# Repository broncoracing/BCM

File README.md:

# Body Control Module
## BR23+ BCM

### Functions:
- Control cooling
  - Fan
  - Water pump
- Actuate shifting
  - Receive shift data over CAN
  - Activate pneumatic shifting actuators
- Any other CAN-controlled outputs

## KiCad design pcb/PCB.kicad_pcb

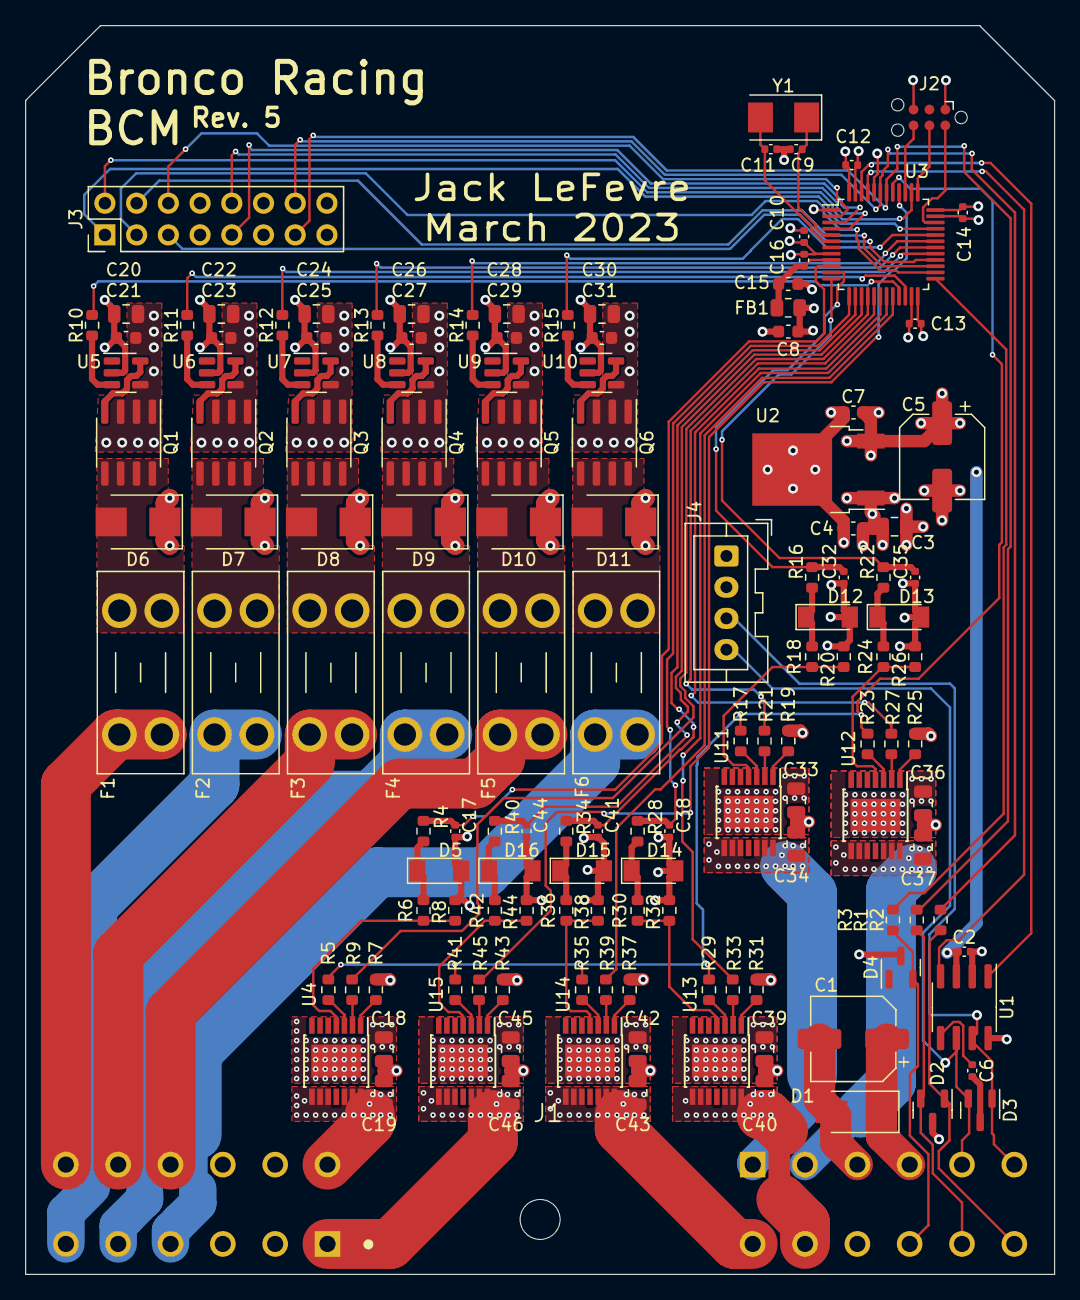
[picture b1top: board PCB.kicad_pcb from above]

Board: 4 copper layers, 82.4 x 100.0 mm, 141 parts (0 on the bottom side), 108 nets.

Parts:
C1, C5: 100uF; CP_Elec_6.3x7.7
C2, C6, C10, C12, C13, C14, C16: 100n; C_0402_1005Metric
C3, C20, C22, C24, C26, C28, C30: 2.2uF; C_0805_2012Metric
C4, C7, C21, C23, C25, C27, C29, C31: 100nF; C_0603_1608Metric
C8: 4u7; C_0603_1608Metric
C9, C11: 30p; C_0402_1005Metric
C15: 1u; C_0603_1608Metric
C17, C32, C35, C38, C41, C44: 220p; C_0402_1005Metric
C18, C33, C36, C39, C42, C45: 100nF >25V; C_0805_2012Metric
C19, C34, C37, C40, C43, C46: 10nF >25V; C_0805_2012Metric
D1: 15-25V; D_SMA
D2, D4: SP0502BAHT; SOT-23
D3: ESDCAN02-2BWY; SOT-23
D5, D12, D13, D14, D15, D16: 7V; D_MiniMELF
D6, D7, D8, D9, D10, D11: SSB43L; D_SMB
F1, F2, F3, F4, F5, F6: Fuse; Fuseholder_Blade_Mini_Keystone_3568
FB1: 100R@100MHz; R_0805_2012Metric
H1: MountingHole_3.2mm_M3
J1: DTM1312PA12PBR008; TE_DTM1312PA12PBR008
J2: TC2030; Tag-Connect_TC2030-IDC-NL_2x03_P1.27mm_Vertical
J3: Conn_02x08_Top_Bottom; PinHeader_2x08_P2.54mm_Vertical
J4: JST B04B-XASK; JST_XA_B04B-XASK-1_1x04_P2.50mm_Vertical
Q1, Q2, Q3, Q4, Q5, Q6: Si4162DY; SOIC-8_3.9x4.9mm_P1.27mm
R1, R2, R3: 470; R_0603_1608Metric
R4, R5, R6, R7, R10, R11, R12, R13, R14, R15, R16, R17, R18, R19, R22, R23, R24, R25, R28, R29, R30, R31, R34, R35, R36, R37, R40, R41, R42, R43: 4.7k; R_0603_1608Metric
R8, R20, R26, R32, R38, R44: 1.2k; R_0603_1608Metric
R9, R21, R27, R33, R39, R45: 47; R_0603_1608Metric
U1: SN65HVD230; SOIC-8_3.9x4.9mm_P1.27mm
U2: LF33_TO252; TO-252-2
U3: STM32F103C8T6; LQFP-48_7x7mm_P0.5mm
U4, U11, U12, U13, U14, U15: BTS7004-1EPP; Infineon_PG-TSDSO-14-22
U5, U6, U7, U8, U9, U10: MCP1416; SOT-23-5
Y1: 8MHz; Crystal_SMD_5032-2Pin_5.0x3.2mm

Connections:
+3.3VA: C15.1, C16.1, FB1.2, U3.9 (VDDA)
+3V3: C2.1, C5.1, C7.1, C8.1, C10.1, C12.1, C13.1, C14.1, FB1.1, J2.1 (VCC), J3.8, J3.16, U1.3 (VCC), U2.3 (VO), U3.1 (VBAT), U3.24 (VDD), U3.36 (VDD), U3.48 (VDD)
+12V: C1.1, C3.1, C4.1, C18.1, C20.1, C21.1, C22.1, C23.1, C24.1, C25.1, C26.1, C27.1, C28.1, C29.1, C30.1, C31.1, C33.1, C36.1, C39.1, C42.1, C45.1, D1.1 (A1), D6.1 (K), D7.1 (K), D8.1 (K), D9.1 (K), D10.1 (K), D11.1 (K), J1.A3, J1.A10, J1.B4, J4.1, U2.1 (VI), U4.15 (VS), U5.2 (Vdd), U6.2 (Vdd), U7.2 (Vdd), U8.2 (Vdd), U9.2 (Vdd), U10.2 (Vdd), U11.15 (VS), U12.15 (VS), U13.15 (VS), U14.15 (VS), U15.15 (VS)
/High-side Channel 0/DEN: R5.1, R17.1, R23.1, R29.1, R35.1, R41.1, U3.41 (PB5)
/High-side Channel 0/Drive: R7.1, U3.16 (PA6)
/High-side Channel 0/Sense: C17.1, R4.1, U3.10 (PA0)
/High-side Channel 1/Drive: R19.1, U3.17 (PA7)
/High-side Channel 1/Sense: C32.1, R16.1, U3.11 (PA1)
/High-side Channel 2/Drive: R25.1, U3.18 (PB0)
/High-side Channel 2/Sense: C35.1, R22.1, U3.12 (PA2)
/High-side Channel 3/Drive: R31.1, U3.19 (PB1)
/High-side Channel 3/Sense: C38.1, R28.1, U3.13 (PA3)
/High-side Channel 4/Drive: R37.1, U3.20 (PB2)
/High-side Channel 4/Sense: C41.1, R34.1, U3.14 (PA4)
/High-side Channel 5/Drive: R43.1, U3.40 (PB4)
/High-side Channel 5/Sense: C44.1, R40.1, U3.15 (PA5)
/Low-side channel 0/Drive: R10.1, U3.21 (PB10)
/Low-side channel 1/Drive: R11.1, U3.22 (PB11)
/Low-side channel 2/Drive: R12.1, U3.29 (PA8)
/Low-side channel 3/Drive: R13.1, U3.30 (PA9)
/Low-side channel 4/Drive: R14.1, U3.31 (PA10)
/Low-side channel 5/Drive: R15.1, U3.32 (PA11)
/STM32/GPIO: R3.1, U3.25 (PB12)
/STM32/HSE_IN: C11.1, U3.6 (PD1), Y1.2
/STM32/HSE_OUT: C9.1, U3.5 (PD0), Y1.1
/STM32/UART_RX: J3.13, R2.1, U3.42 (PB6)
/STM32/UART_TX: J3.14, R1.2, U3.43 (PB7)
/STM32/UU0: J3.1, U3.33 (PA12)
/STM32/UU1: J3.2, U3.38 (PA15)
/STM32/UU2: J3.3, U3.26 (PB13)
/STM32/UU3: J3.4, U3.27 (PB14)
/STM32/UU4: J3.5, U3.28 (PB15)
/STM32/UU5: J3.6, U3.2 (PC13)
/STM32/UU6: J3.9, U3.3 (PC14)
/STM32/UU7: J3.10, U3.4 (PC15)
CAN+: D3.1 (K), J1.B6, J4.3, U1.7 (CANH)
CAN-: D3.2 (K), J1.B5, J4.4, U1.6 (CANL)
CANRX: U1.4 (R), U3.45 (PB8)
CANTX: U1.1 (D), U3.46 (PB9)
GND: C1.2, C2.2, C3.2, C4.2, C5.2, C7.2, C8.2, C9.2, C10.2, C11.2, C12.2, C13.2, C14.2, C15.2, C16.2, C17.2, C18.2, C19.2, C20.2, C21.2, C22.2, C23.2, C24.2, C25.2, C26.2, C27.2, C28.2, C29.2, C30.2, C31.2, C32.2, C33.2, C34.2, C35.2, C36.2, C37.2, C38.2, C39.2, C40.2, C41.2, C42.2, C43.2, C44.2, C45.2, C46.2, D1.2 (A2), D2.3 (A), D4.3 (A), D5.2 (A), D12.2 (A), D13.2 (A), D14.2 (A), D15.2 (A), D16.2 (A), J1.A2, J1.A11, J1.B3, J1.B10, J2.5 (GND), J3.7, J3.12, J3.15, J4.2, Q1.1 (S), Q1.2 (S), Q1.3 (S), Q2.1 (S), Q2.2 (S), Q2.3 (S), Q3.1 (S), Q3.2 (S), Q3.3 (S), Q4.1 (S), Q4.2 (S), Q4.3 (S), Q5.1 (S), Q5.2 (S), Q5.3 (S), Q6.1 (S), Q6.2 (S), Q6.3 (S), R8.2, R9.2, R20.2, R21.2, R26.2, R27.2, R32.2, R33.2, R38.2, R39.2, R44.2, R45.2, U1.2 (GND), U1.8 (Rs), U2.2 (GND), U3.8 (VSSA), U3.23 (VSS), U3.35 (VSS), U3.44 (BOOT0), U3.47 (VSS), U5.4 (GND), U6.4 (GND), U7.4 (GND), U8.4 (GND), U9.4 (GND), U10.4 (GND)
H0: C19.1, J1.A12, U4.8 (OUT), U4.9 (OUT), U4.10 (OUT), U4.12 (OUT), U4.13 (OUT), U4.14 (OUT)
H1: C34.1, J1.B1, U11.8 (OUT), U11.9 (OUT), U11.10 (OUT), U11.12 (OUT), U11.13 (OUT), U11.14 (OUT)
H2: C37.1, J1.B2, U12.8 (OUT), U12.9 (OUT), U12.10 (OUT), U12.12 (OUT), U12.13 (OUT), U12.14 (OUT)
H3: C40.1, J1.B11, U13.8 (OUT), U13.9 (OUT), U13.10 (OUT), U13.12 (OUT), U13.13 (OUT), U13.14 (OUT)
H4: C43.1, J1.B12, U14.8 (OUT), U14.9 (OUT), U14.10 (OUT), U14.12 (OUT), U14.13 (OUT), U14.14 (OUT)
H5: C46.1, J1.A1, U15.8 (OUT), U15.9 (OUT), U15.10 (OUT), U15.12 (OUT), U15.13 (OUT), U15.14 (OUT)
IO: D4.2 (K), J1.B9, R3.2
L0: F1.2, J1.A7
L1: F2.2, J1.A6
L2: F3.2, J1.A8
L3: F4.2, J1.A5
L4: F5.2, J1.A9
L5: F6.2, J1.A4
unnamed: C6.1, U1.5 (Vref)
unnamed: C6.2, D3.3 (A)
unnamed: D5.1 (K), R4.2, R6.2
unnamed: D6.2 (A), F1.1, Q1.5 (D), Q1.6 (D), Q1.7 (D), Q1.8 (D)
unnamed: D7.2 (A), F2.1, Q2.5 (D), Q2.6 (D), Q2.7 (D), Q2.8 (D)
unnamed: D8.2 (A), F3.1, Q3.5 (D), Q3.6 (D), Q3.7 (D), Q3.8 (D)
unnamed: D9.2 (A), F4.1, Q4.5 (D), Q4.6 (D), Q4.7 (D), Q4.8 (D)
unnamed: D10.2 (A), F5.1, Q5.5 (D), Q5.6 (D), Q5.7 (D), Q5.8 (D)
unnamed: D11.2 (A), F6.1, Q6.5 (D), Q6.6 (D), Q6.7 (D), Q6.8 (D)
unnamed: D12.1 (K), R16.2, R18.2
unnamed: D13.1 (K), R22.2, R24.2
unnamed: D14.1 (K), R28.2, R30.2
unnamed: D15.1 (K), R34.2, R36.2
unnamed: D16.1 (K), R40.2, R42.2
unnamed: Q1.4 (G), U5.5 (OUT)
unnamed: Q2.4 (G), U6.5 (OUT)
unnamed: Q3.4 (G), U7.5 (OUT)
unnamed: Q4.4 (G), U8.5 (OUT)
unnamed: Q5.4 (G), U9.5 (OUT)
unnamed: Q6.4 (G), U10.5 (OUT)
unnamed: R5.2, U4.3 (DEN)
unnamed: R6.1, R8.1, U4.4 (IS)
unnamed: R7.2, U4.2 (IN)
unnamed: R9.1, U4.1 (GND)
unnamed: R10.2, U5.3 (IN)
unnamed: R11.2, U6.3 (IN)
unnamed: R12.2, U7.3 (IN)
unnamed: R13.2, U8.3 (IN)
unnamed: R14.2, U9.3 (IN)
unnamed: R15.2, U10.3 (IN)
unnamed: R17.2, U11.3 (DEN)
unnamed: R18.1, R20.1, U11.4 (IS)
unnamed: R19.2, U11.2 (IN)
unnamed: R21.1, U11.1 (GND)
unnamed: R23.2, U12.3 (DEN)
unnamed: R24.1, R26.1, U12.4 (IS)
unnamed: R25.2, U12.2 (IN)
unnamed: R27.1, U12.1 (GND)
unnamed: R29.2, U13.3 (DEN)
unnamed: R30.1, R32.1, U13.4 (IS)
unnamed: R31.2, U13.2 (IN)
unnamed: R33.1, U13.1 (GND)
unnamed: R35.2, U14.3 (DEN)
unnamed: R36.1, R38.1, U14.4 (IS)
unnamed: R37.2, U14.2 (IN)
unnamed: R39.1, U14.1 (GND)
unnamed: R41.2, U15.3 (DEN)
unnamed: R42.1, R44.1, U15.4 (IS)
unnamed: R43.2, U15.2 (IN)
unnamed: R45.1, U15.1 (GND)
SWCLK: J2.4 (SWCLK), U3.37 (PA14)
SWDIO: J2.2 (SWDIO), U3.34 (PA13)
SWO: J2.6 (SWO), U3.39 (PB3)
UART_RX: D2.2 (K), J1.B8, R2.2
UART_TX: D2.1 (K), J1.B7, R1.1

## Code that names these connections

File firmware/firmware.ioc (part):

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Mcu.Name=STM32F103C(8-B)Tx
Mcu.Package=LQFP48
Mcu.UserName=STM32F103C8Tx
PA0-WKUP.Signal=ADCx_IN0
PA1.Signal=ADCx_IN1
PA10.Signal=S_TIM1_CH3
PA11.Signal=S_TIM1_CH4
PA13.Mode=Trace_Asynchronous_SW
PA13.Signal=SYS_JTMS-SWDIO
PA14.Mode=Trace_Asynchronous_SW
PA14.Signal=SYS_JTCK-SWCLK
PA2.Signal=ADCx_IN2
PA3.Signal=ADCx_IN3
PA4.Signal=ADCx_IN4
PA5.Signal=ADCx_IN5
PA6.GPIOParameters=GPIO_Label
PA6.GPIO_Label=H0
PA6.Signal=GPIO_Output
PA7.GPIOParameters=GPIO_Label
PA7.GPIO_Label=H1
PA7.Signal=GPIO_Output
PA8.Signal=S_TIM1_CH1
PA9.Signal=S_TIM1_CH2
PB0.GPIOParameters=GPIO_Label
PB0.GPIO_Label=H2
PB0.Signal=GPIO_Output
PB1.GPIOParameters=GPIO_Label
PB1.GPIO_Label=H3
PB1.Signal=GPIO_Output
PB10.Signal=S_TIM2_CH3
PB11.Signal=S_TIM2_CH4
PB2.GPIOParameters=GPIO_Label
PB2.GPIO_Label=H4
PB2.Signal=GPIO_Output
PB3.Mode=Trace_Asynchronous_SW
PB3.Signal=SYS_JTDO-TRACESWO
PB4.GPIOParameters=GPIO_Label
PB4.GPIO_Label=H5
PB4.Signal=GPIO_Output
PB5.GPIOParameters=GPIO_Label
PB5.GPIO_Label=DEN
PB5.Signal=GPIO_Output
PB6.Mode=Asynchronous
PB6.Signal=USART1_TX
PB7.Mode=Asynchronous
PB7.Signal=USART1_RX
PB8.GPIOParameters=GPIO_PuPd,GPIO_Mode
PB8.GPIO_Mode=GPIO_MODE_INPUT
PB8.GPIO_PuPd=GPIO_NOPULL
PB8.Mode=CAN_Activate
PB8.Signal=CAN_RX
PB9.Mode=CAN_Activate
PB9.Signal=CAN_TX
PD0-OSC_IN.Mode=HSE-External-Oscillator
PD0-OSC_IN.Signal=RCC_OSC_IN
PD1-OSC_OUT.Mode=HSE-External-Oscillator
PD1-OSC_OUT.Signal=RCC_OSC_OUT
RCC.SYSCLKFreq_VALUE=72000000
RCC.SYSCLKSource=RCC_SYSCLKSOURCE_PLLCLK
board=custom

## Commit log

2021-10-08 Initialize cubeMX project
2021-10-08 add can-ids submodule
2021-10-25 add components
2021-10-27 Initialize Cmake workflow with default template
2021-10-27 Add arm compiler to dependencies
2021-10-27 Fix arm gcc implementation, update runner target dir
2021-10-27 Make build workflow
2021-10-27 Change default working dir, cleanup
2021-10-27 Add build directory to gitignore
2021-10-27 revert this: modify main.c to test build pipeline
2021-10-27 Allow manual workflow running, update triggers
2021-10-27 Fix syntax errors
2021-10-27 more syntax fixes
2021-10-27 Remove reference to unused script
2021-10-27 env vars are stupid sometimes
2021-10-27 remove make check and distcheck
2021-10-27 Add Make build workflow (#3)
    * Add github workflow to verify that changes pushed to ./firmware build
2021-10-27 modify main.c to test build pipeline
2021-10-27 intentionally cause build to fail to test pipeline
2021-10-27 Add name so status check can be required from branch protection
2021-10-27 create failing build to test CI
2021-11-29 Updated parts and routing
    Updated schematic to use new Smart switches and Micro. Also changed the drive channels
2022-01-08 Corrected schematic
2022-01-26 Corrected STM32 pinout, changed designators, added decoupling caps, and corrected passives for fets
2022-01-26 Fixed net labels and other errors from previous commit
2022-01-31 Fixed connector pinout
2022-02-01 Finished layout & routing
2022-02-02 Added magical crystal power
2022-02-02 Fix designator position
2022-02-02 Final schematic changes
2022-02-02 Added TVS protection to PCB
2022-02-13 Created schematic and PCB (#6)
    * add components
    * Updated parts and routing
    Updated schematic to use new Smart switches and Micro. Also changed the drive channels
    * Corrected schematic
    * Corrected STM32 pinout, changed designators, added decoupling caps, and corrected passives for fets
    * Fixed net labels and other errors from previous commit
2022-03-22 Added pdf schematic
2022-03-22 Added pdf schematic (#7)
2022-03-25 Cleanup cubemx project files
2022-03-25 Initial BCM firmware * Configure mbed * set up main program loop * set up CAN * update gitignore * update headers
2022-04-02 Create build CI workflow
    Shamelessly copy and paste the build workflow from blinky
2022-04-02 Add step to save artifact from build
2022-04-02 Remove old workflow
2022-04-02 Update build CI workflow (#10)
    * Create build CI workflow
    * Shamelessly copy and paste the build workflow from blinky
    * Add step to save artifact from build
    * Remove old workflow
2022-04-02 fix build workflow name
2022-04-02 Fix workflow
2022-04-02 Fix working directory, only trigger on firmware changes
2022-04-02 fix indentation
2022-04-02 checkout submodules in workflow
2022-04-02 change mbed-cli to V1 because linker is stupid
2022-04-02 fix env variable in path
2022-04-02 Fix path for mbed-cli v1
2022-04-02 set correct build directory based on working directory
2022-04-02 forgot pipe
2022-04-02 fix build directory
2022-04-02 fix build directory again
2022-04-02 fix path again again
2022-04-02 Implement BCM firmware
2022-04-02 Fix submodules
2022-04-05 Add debug print statements, set fan PWM period
2022-04-05 Address feedback, cleanup formatting
2022-04-05 Fix pin reset function to address pointer issues
2022-04-28 Add watchdog
2022-05-03 Tweak shift times, move watchdog
2022-05-10 Testing fixes - change water temp to celsius - update print statements - update can ids - Update header params
2022-05-10 Better printing, cleanup - Cleanup/organize header - Consolidate repeated print statements - Add more init confirmation statements - Format existing print statements
2022-05-11 Move watchdog, update ETC printout
2022-05-12 Fix build filename
2022-05-12 fix filename again again again
2022-05-12 Add etc fault in from bspd, disable fault recovery
2022-05-17 Added shift delay
2022-05-17 disable latch on non-bspd fault
2022-05-18 not working
2022-07-01 Remove shift delay, cleanup
2022-07-01 Implement BCM firmware (#11)
    * Implement BCM firmware
    * Fix submodules
    * Add debug print statements, set fan PWM period
    * Address feedback, cleanup formatting
    * Fix pin reset function to address pointer issues
    * Add watchdog
2022-10-17 Nuked the altium stuff
2022-10-17 Updated to new template
2022-10-31 Finished schematic
2022-10-31 Started layout
2022-11-02 Worked on layout
2022-11-02 Added missing files for kibot
2022-11-03 Worked on layout some more
2022-11-18 Finish layout (still needs memes)
2022-11-18 Fixed ERC
2022-11-18 Added debug/test header
2023-01-17 Switched to non-sketchy regulator
2023-02-01 Bottom text
2023-02-09 Switch to KiCAD, made rev 5 (#12)
    * Nuked the altium stuff
    * Updated to new template
    * Finished schematic
    * Started layout
    * Worked on layout
    * Added missing files for kibot
2023-02-24 Disconnected NRESET
2023-03-08 Udpate date/revision of BCM
2023-03-16 Made test firmware
2023-03-16 Add can IDs
2023-03-26 Correct PCB to fix firmware flashing (#14)
    * Disconnected NRESET
    * Udpate date/revision of BCM
2023-03-26 Fix fw to work with bootloader
2023-03-26 remove unnecessary file
2023-04-13 Honk
2023-05-01 Update for IC car
2023-05-01 BCM Firmware (#15)
    * Disconnected NRESET
    * Udpate date/revision of BCM
    * Made test firmware
    * Add can IDs
    * Fix fw to work with bootloader
    * remove unnecessary file
2023-05-11 fixed pwm init, add fuel pump output
2023-05-13 removed testing stuff
2023-08-31 Updated CAN IDs
2023-09-01 fix dumbass fuckup
2024-03-04 update gitignore
2024-04-30 bump can ids
2024-04-30 ev bcm fw
2024-05-01 fix duty cycle range
2024-06-21 fix fan problem
